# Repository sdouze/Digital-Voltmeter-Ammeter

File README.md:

# Voltmeter-Ammeter
Arduino Based Volt-Amp Meter

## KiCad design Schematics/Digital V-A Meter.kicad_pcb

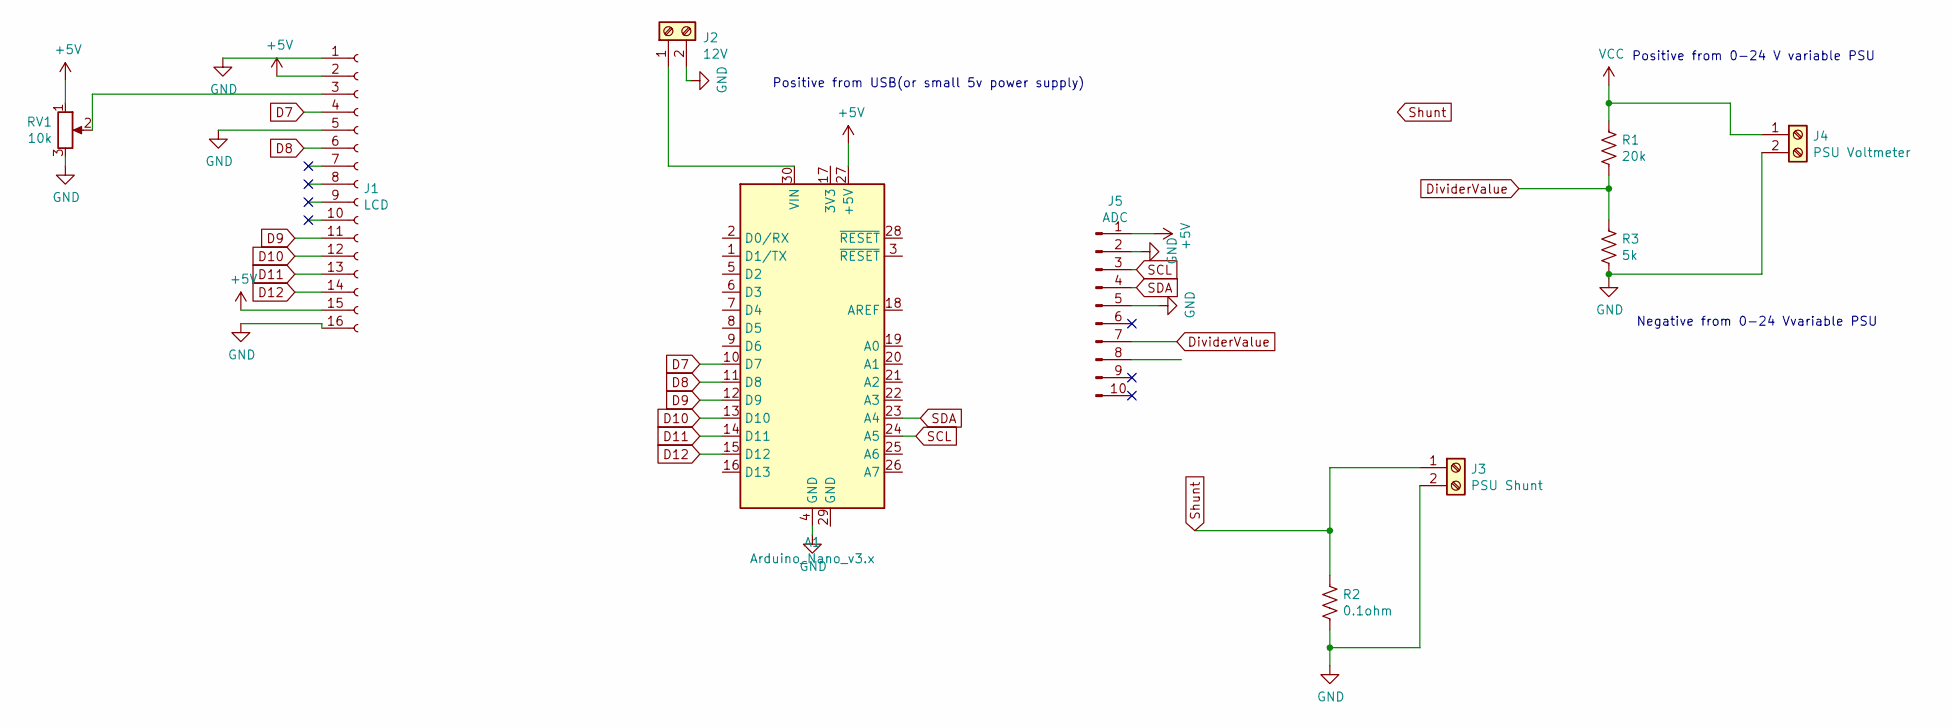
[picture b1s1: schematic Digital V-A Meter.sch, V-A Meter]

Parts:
A1: Arduino_Nano_v3.x; Arduino_Nano
J1: LCD; PinHeader_1x16_P2.54mm_Vertical
J2: 12V; Molex_KK-254_AE-6410-02A_1x02_P2.54mm_Vertical
J3: PSU Shunt; Molex_KK-254_AE-6410-02A_1x02_P2.54mm_Vertical
J4: PSU Voltmeter; Molex_KK-254_AE-6410-02A_1x02_P2.54mm_Vertical
J5: ADC; PinHeader_1x10_P2.54mm_Vertical
R1: 20k; R_Axial_DIN0204_L3.6mm_D1.6mm_P7.62mm_Horizontal
R2: 0.1ohm; R_Axial_DIN0922_L20.0mm_D9.0mm_P25.40mm_Horizontal
R3: 5k; R_Axial_DIN0204_L3.6mm_D1.6mm_P7.62mm_Horizontal
RV1: 10k; Potentiometer_Runtron_RM-065_Vertical

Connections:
+5V: A1.27 (+5V), J1.2, J1.15, J5.1, RV1.1
D7: A1.10 (D7), J1.4
D8: A1.11 (D8), J1.6
D9: A1.12 (D9), J1.11
D10: A1.13 (D10), J1.12
D11: A1.14 (D11), J1.13
D12: A1.15 (D12), J1.14
DividerValue: J5.7, R1.2, R3.1
GND: A1.4 (GND), A1.29 (GND), J1.1, J1.5, J1.16, J2.2, J3.2, J4.2, J5.2, J5.5, R2.2, R3.2, RV1.3
unnamed: A1.30 (VIN), J2.1
unnamed: J1.3, RV1.2
SCL: A1.24 (A5), J5.3
SDA: A1.23 (A4), J5.4
Shunt: J3.1, R2.1
VCC: J4.1, R1.1

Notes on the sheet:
Positive from 0-24 V variable PSU
Negative from 0-24 Vvariable PSU
Positive from USB(or small 5v power supply)

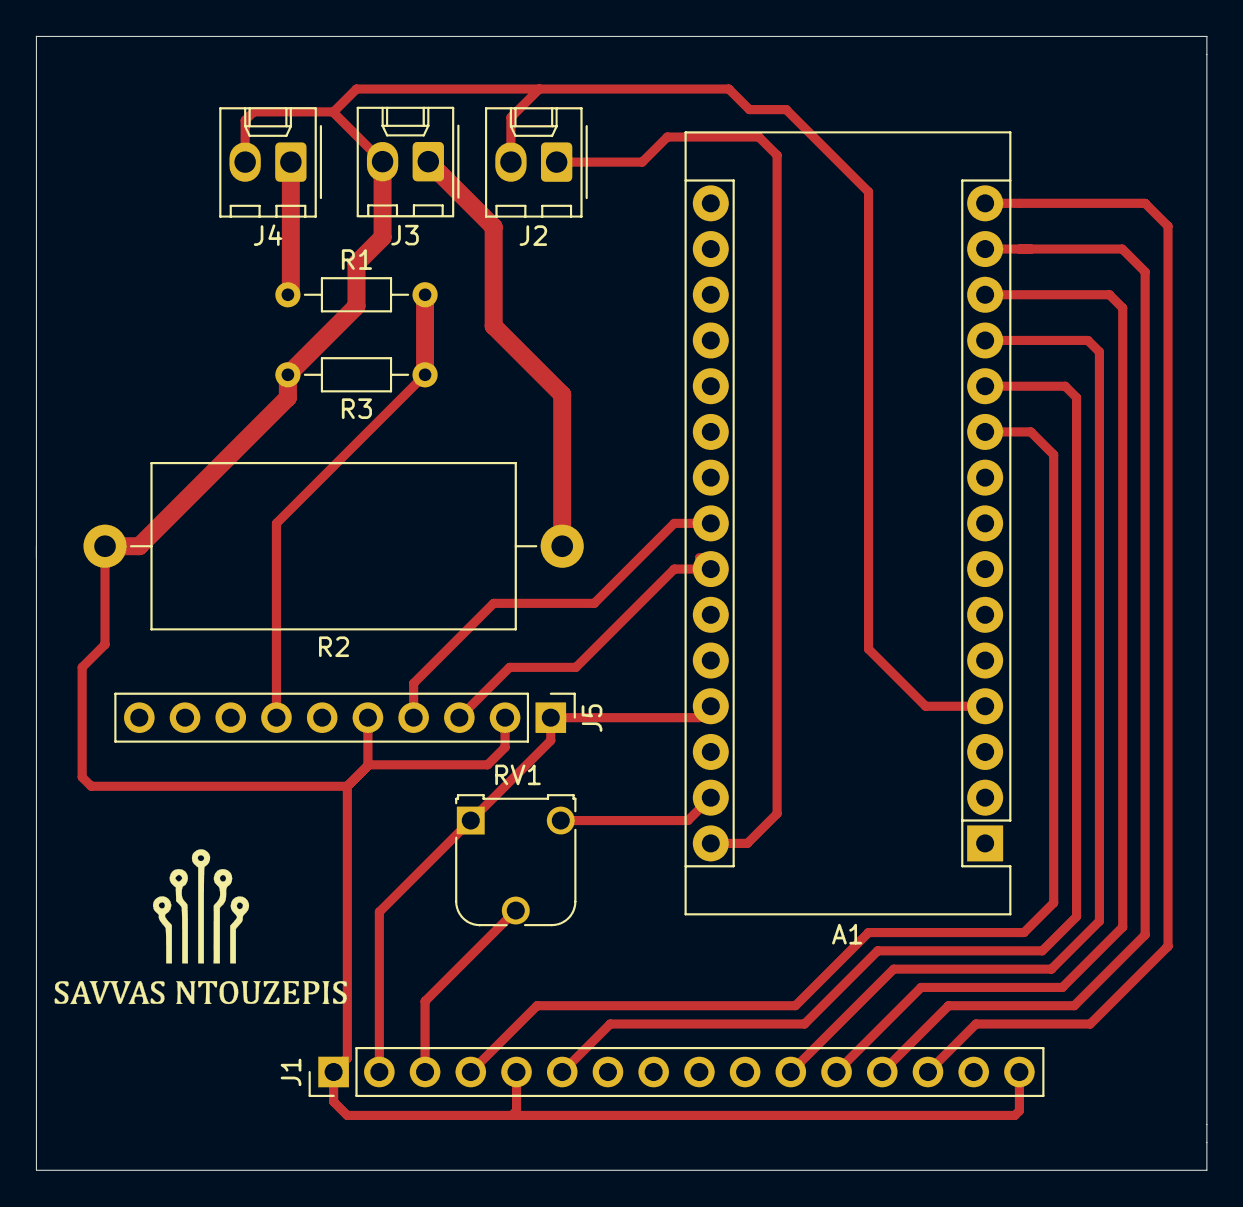
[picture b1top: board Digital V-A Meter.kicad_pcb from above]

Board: 2 copper layers, 65.0 x 63.0 mm, 10 parts (0 on the bottom side), 15 nets.

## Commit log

2021-06-09 Add files via upload
    Schematic and PCB made with KiCad
2021-06-09 Still WIP. Current measurement is faulty
